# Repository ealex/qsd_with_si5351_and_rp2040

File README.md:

# qsd_with_si5351_and_rp2040
Tayloe QSD with SI5351 clock and RP2040 as an USB and UI controller

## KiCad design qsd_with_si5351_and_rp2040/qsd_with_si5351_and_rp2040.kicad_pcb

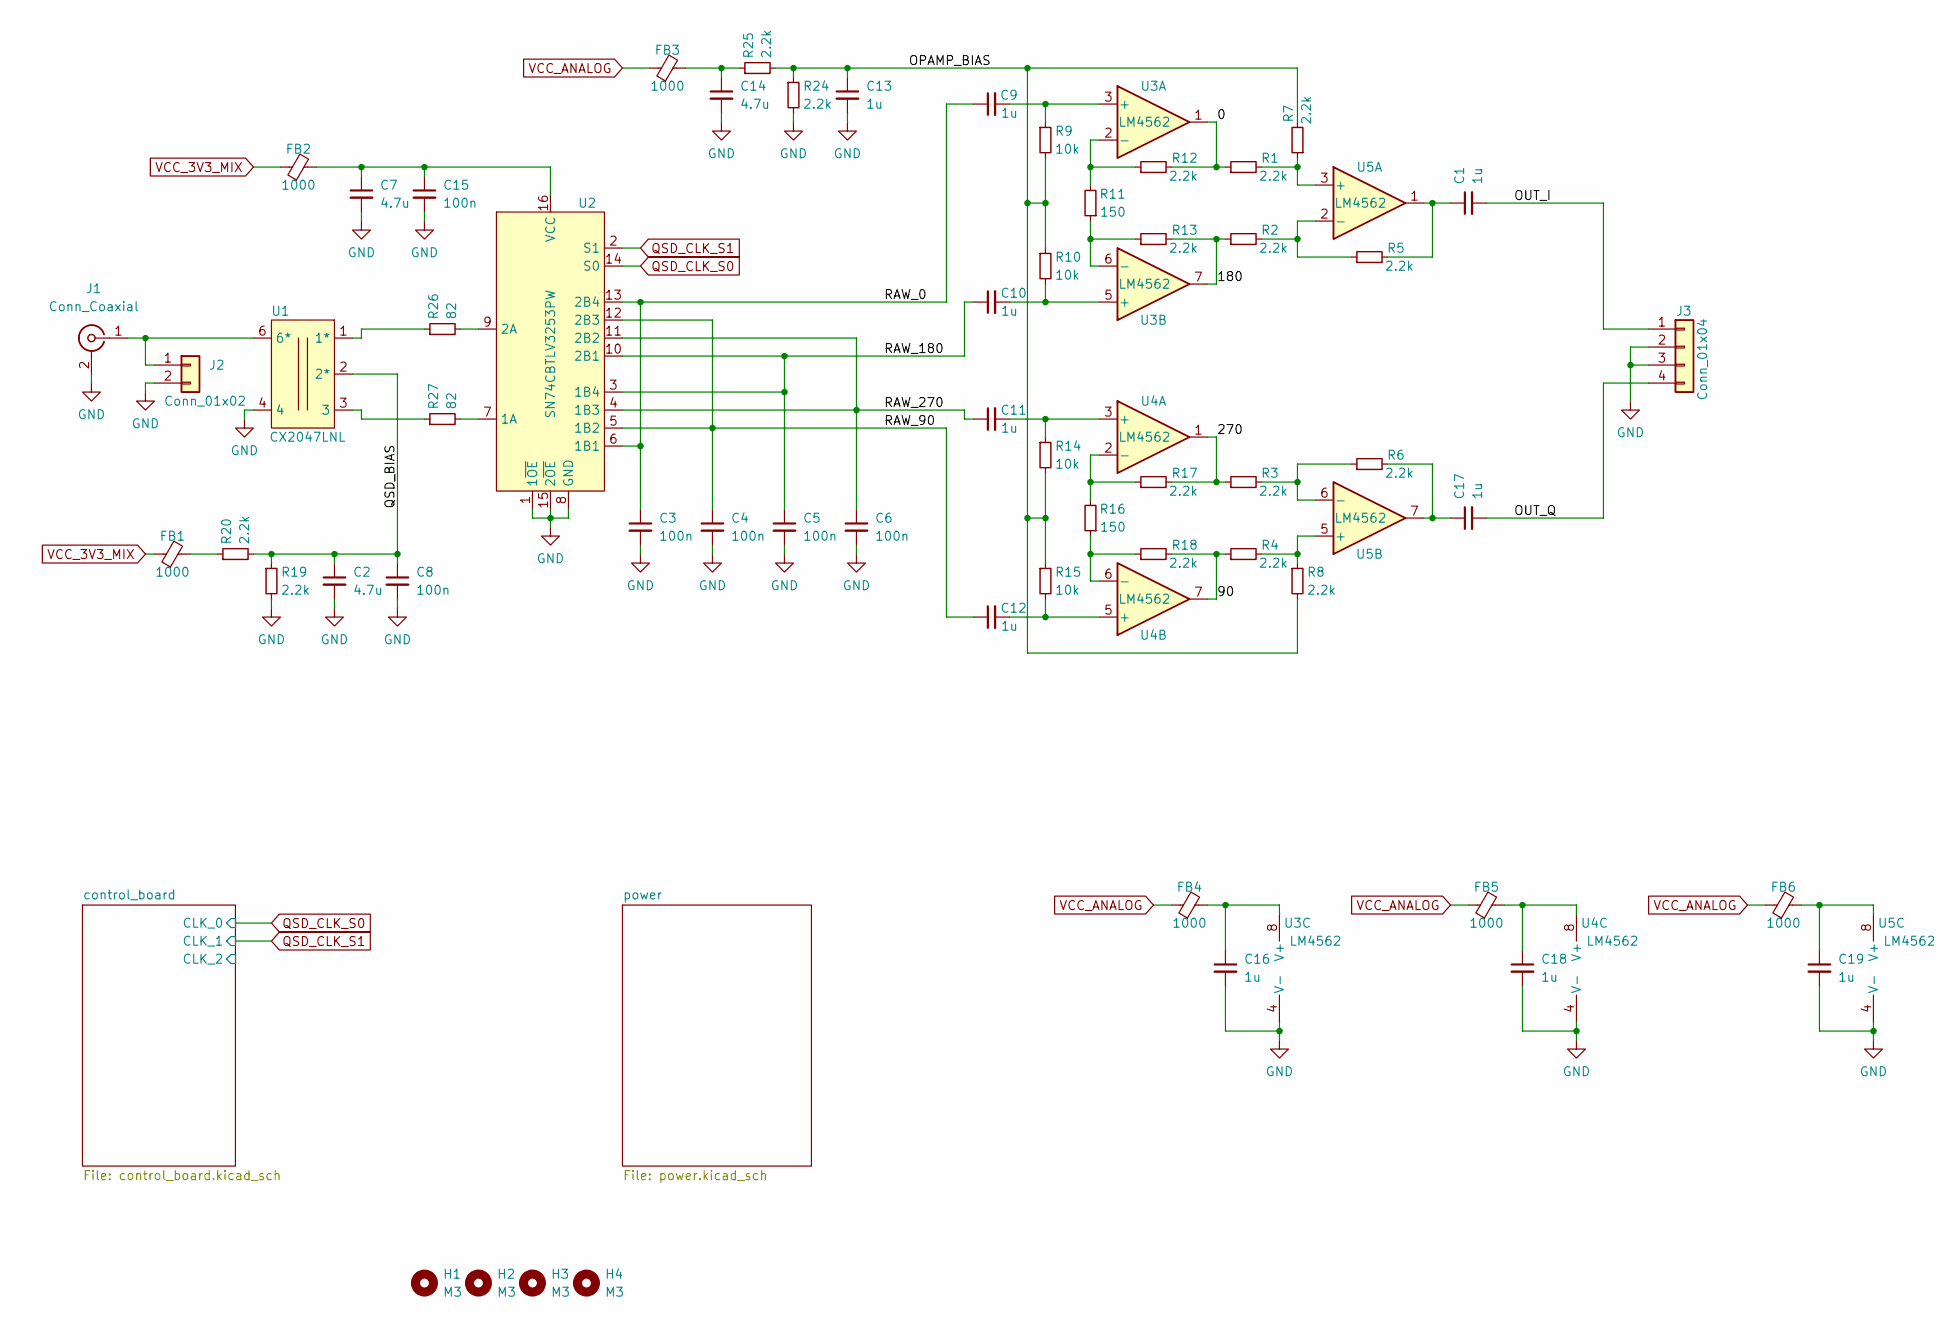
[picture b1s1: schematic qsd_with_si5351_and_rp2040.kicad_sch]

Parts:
C1, C9, C10, C11, C12, C13, C16, C17, C18, C19: 1u; C_0805_2012Metric
C2, C7, C14: 4.7u; C_0805_2012Metric
C3, C4, C5, C6, C8, C15: 100n; C_0805_2012Metric
FB1, FB2, FB3, FB4, FB5, FB6: 1000; L_0805_2012Metric_Pad1.05x1.20mm_HandSolder
H1, H2, H3, H4: M3; MountingHole_3.2mm_M3_DIN965_Pad_TopBottom
J1: Conn_Coaxial; 60312202114508
J2: Conn_01x02; PinHeader_1x02_P2.54mm_Vertical
J3: Conn_01x04; PinHeader_1x04_P2.54mm_Vertical
R1, R2, R3, R4, R5, R6, R7, R8, R12, R13, R17, R18, R19, R20, R24, R25: 2.2k; R_0805_2012Metric_Pad1.20x1.40mm_HandSolder
R9, R10, R14, R15: 10k; R_0805_2012Metric_Pad1.20x1.40mm_HandSolder
R11, R16: 150; R_0805_2012Metric_Pad1.20x1.40mm_HandSolder
R26, R27: 82; R_0805_2012Metric_Pad1.20x1.40mm_HandSolder
U1: CX2047LNL
U2: SN74CBTLV3253PW; TSSOP-16_4.4x5mm_P0.65mm
U3, U4, U5: LM4562; SO-8_3.9x4.9mm_P1.27mm

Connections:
/0: R1.1, R12.2, U3.1
/90: R4.1, R18.2, U4.7
/180: R2.1, R13.2, U3.7
/270: R3.1, R17.2, U4.1
/OPAMP_BIAS: C13.1, R7.2, R8.2, R9.2, R10.1, R14.2, R15.1, R24.1, R25.2
/OUT_I: C1.2, J3.1
/OUT_Q: C17.2, J3.4
/QSD_BIAS: C2.1, C8.1, R19.1, R20.2, U1.2 (2*)
/RAW_0: C3.1, C9.1, U2.6 (1B1), U2.13 (2B4)
/RAW_90: C4.1, C12.1, U2.5 (1B2), U2.12 (2B3)
/RAW_180: C5.1, C10.1, U2.3 (1B4), U2.10 (2B1)
/RAW_270: C6.1, C11.1, U2.4 (1B3), U2.11 (2B2)
unnamed: C1.1, R5.2, U5.1
unnamed: C9.2, R9.1, U3.3 (+)
unnamed: C10.2, R10.2, U3.5 (+)
unnamed: C11.2, R14.1, U4.3 (+)
unnamed: C12.2, R15.2, U4.5 (+)
unnamed: C14.1, FB3.2, R25.1
unnamed: C7.1, C15.1, FB2.2, U2.16 (VCC)
unnamed: C16.1, FB4.2, U3.8 (V+)
unnamed: C17.1, R6.2, U5.7
unnamed: C18.1, FB5.2, U4.8 (V+)
unnamed: C19.1, FB6.2, U5.8 (V+)
unnamed: FB1.2, R20.1
unnamed: J1.1 (In), J2.1, U1.6 (6*)
unnamed: R1.2, R7.1, U5.3 (+)
unnamed: R2.2, R5.1, U5.2 (-)
unnamed: R3.2, R6.1, U5.6 (-)
unnamed: R4.2, R8.1, U5.5 (+)
unnamed: R11.1, R13.1, U3.6 (-)
unnamed: R11.2, R12.1, U3.2 (-)
unnamed: R16.1, R18.1, U4.6 (-)
unnamed: R16.2, R17.1, U4.2 (-)
unnamed: R26.1, U1.1 (1*)
unnamed: R26.2, U2.9 (2A)
unnamed: R27.1, U1.3
unnamed: R27.2, U2.7 (1A)
QSD_CLK_S0: U2.14 (S0); also elsewhere on the board
QSD_CLK_S1: U2.2 (S1); also elsewhere on the board
VCC_3V3_MIX: FB1.1, FB2.1; also elsewhere on the board
VCC_ANALOG: FB3.1, FB4.1, FB5.1, FB6.1; also elsewhere on the board

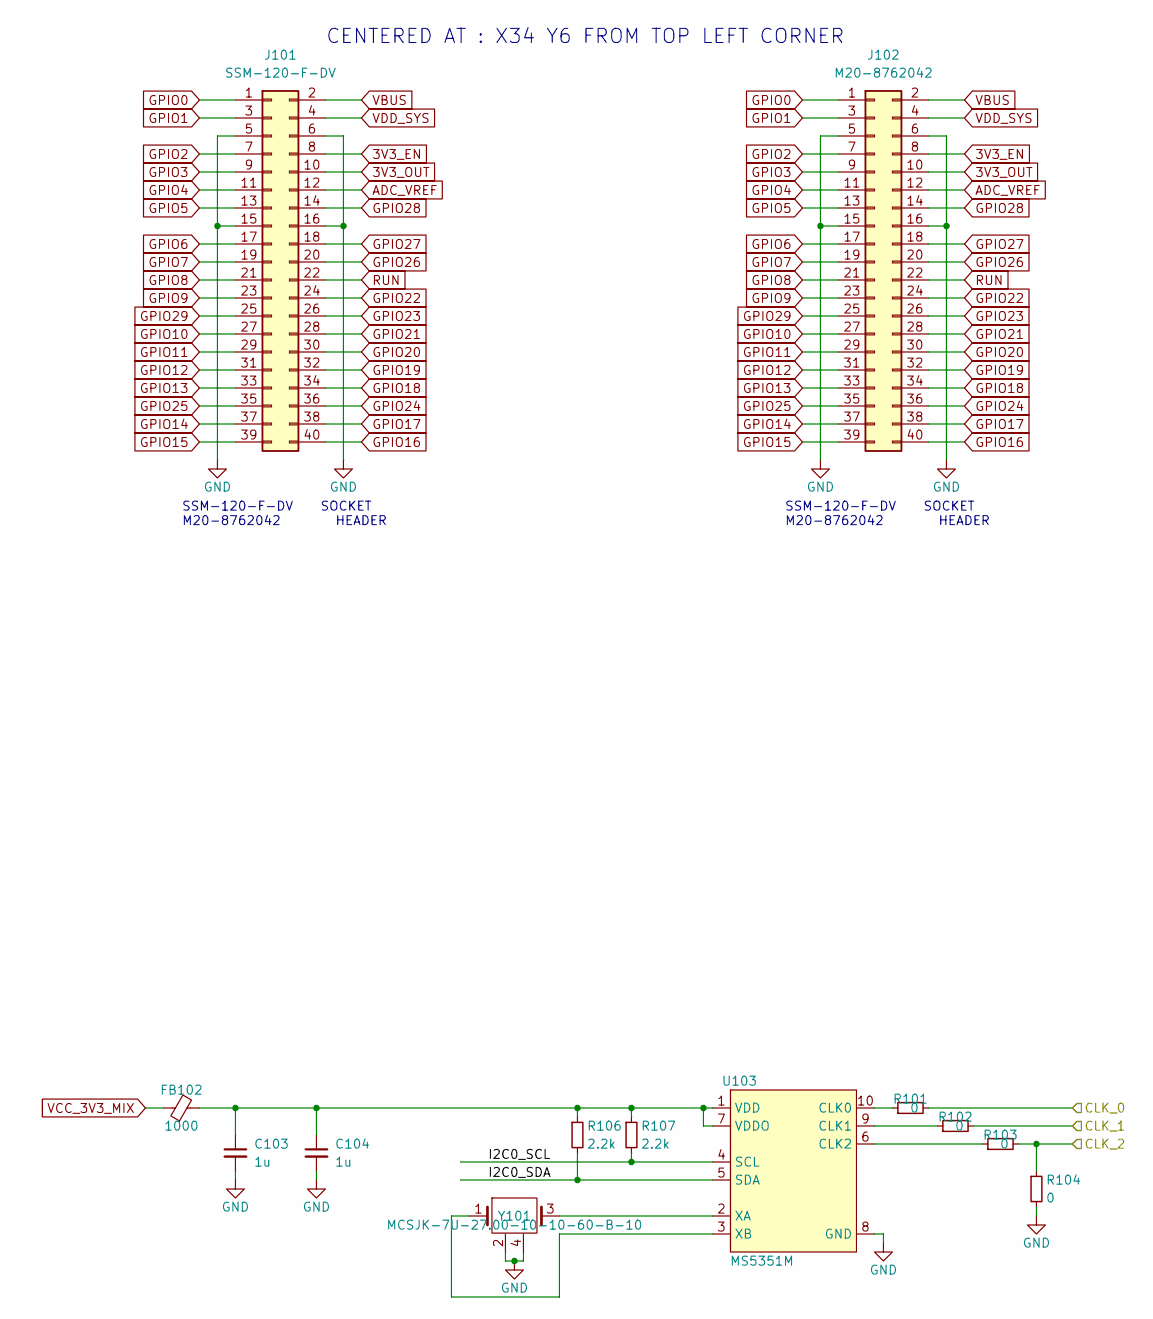
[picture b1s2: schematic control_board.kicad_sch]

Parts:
C103, C104: 1u; C_0805_2012Metric
FB102: 1000; L_0805_2012Metric_Pad1.05x1.20mm_HandSolder
J101: SSM-120-F-DV; PinSocket_2x20_P2.54mm_Vertical_SMD
J102: M20-8762042; PinHeader_2x20_P2.54mm_Vertical_SMD
R101, R102, R103, R104: 0; R_0805_2012Metric_Pad1.20x1.40mm_HandSolder
R106, R107: 2.2k; R_0805_2012Metric_Pad1.20x1.40mm_HandSolder
U103: MS5351M; MSOP-10_3x3mm_P0.5mm
Y101: MCSJK-7U-27.00-10-10-60-B-10; Crystal_SMD_3225-4Pin_3.2x2.5mm

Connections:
3V3_EN: J101.8, J102.8
3V3_OUT: J101.10, J102.10; also elsewhere on the board
/control_board/CLK_2: R103.2, R104.1
/control_board/I2C0_SCL: R107.2, U103.4 (SCL)
/control_board/I2C0_SDA: R106.2, U103.5 (SDA)
ADC_VREF: J101.12, J102.12
GPIO0: J101.1, J102.1
GPIO1: J101.3, J102.3
GPIO2: J101.7, J102.7
GPIO3: J101.9, J102.9
GPIO4: J101.11, J102.11
GPIO5: J101.13, J102.13
GPIO6: J101.17, J102.17
GPIO7: J101.19, J102.19
GPIO8: J101.21, J102.21
GPIO9: J101.23, J102.23
GPIO10: J101.27, J102.27
GPIO11: J101.29, J102.29
GPIO12: J101.31, J102.31
GPIO13: J101.33, J102.33
GPIO14: J101.37, J102.37
GPIO15: J101.39, J102.39
GPIO16: J101.40, J102.40
GPIO17: J101.38, J102.38
GPIO18: J101.34, J102.34
GPIO19: J101.32, J102.32
GPIO20: J101.30, J102.30
GPIO21: J101.28, J102.28
GPIO22: J101.24, J102.24
GPIO23: J101.26, J102.26
GPIO24: J101.36, J102.36
GPIO25: J101.35, J102.35
GPIO26: J101.20, J102.20
GPIO27: J101.18, J102.18
GPIO28: J101.14, J102.14
GPIO29: J101.25, J102.25
unnamed: R102.1, U103.9 (CLK1)
unnamed: R103.1, U103.6 (CLK2)
unnamed: C103.1, C104.1, FB102.2, R106.1, R107.1, U103.1 (VDD), U103.7 (VDDO)
unnamed: U103.2 (XA), Y101.3
unnamed: U103.3 (XB), Y101.1
unnamed: R101.1, U103.10 (CLK0)
QSD_CLK_S0: R101.2; also elsewhere on the board
QSD_CLK_S1: R102.2; also elsewhere on the board
RUN: J101.22, J102.22
VBUS: J101.2, J102.2
VCC_3V3_MIX: FB102.1; also elsewhere on the board
VDD_SYS: J101.4, J102.4; also elsewhere on the board

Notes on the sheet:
SSM-120-F-DV SOCKET M20-8762042 HEADER
CENTERED AT : X34 Y6 FROM TOP LEFT CORNER

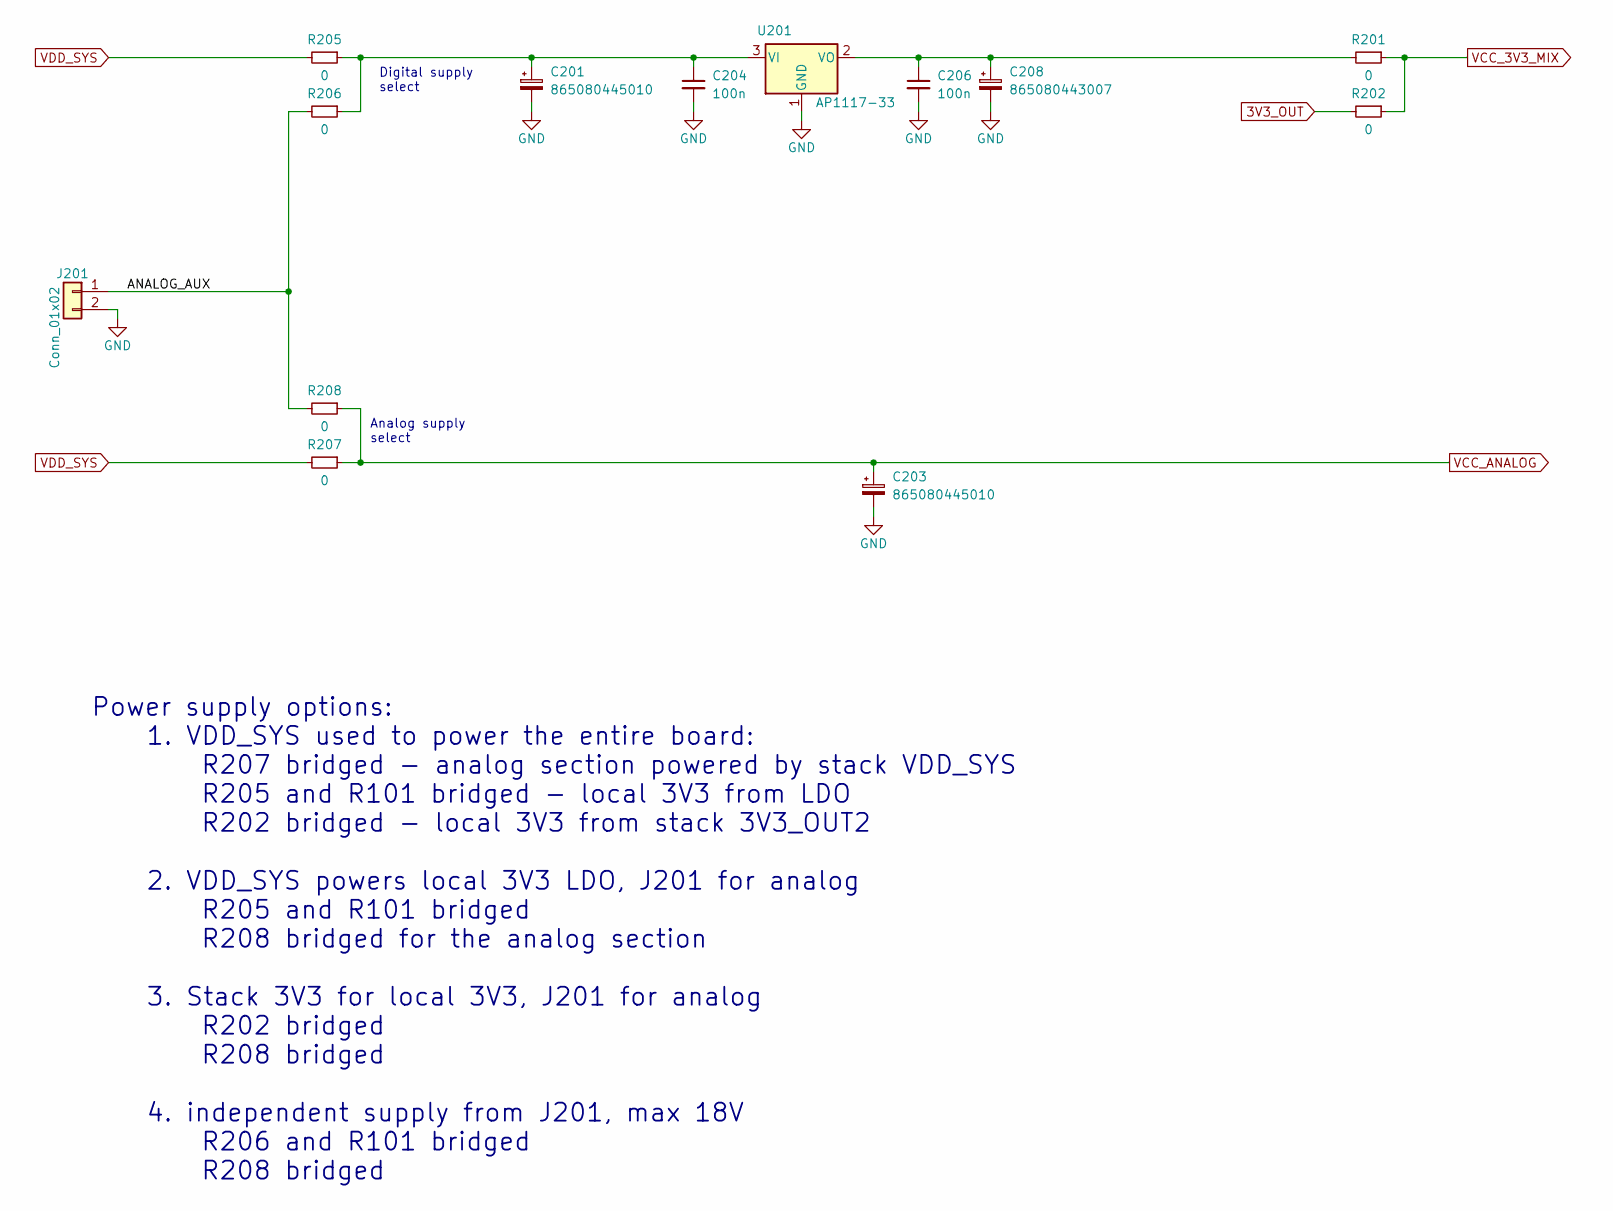
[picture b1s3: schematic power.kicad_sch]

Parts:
C201, C203: 865080445010
C204, C206: 100n; C_0805_2012Metric_Pad1.18x1.45mm_HandSolder
C208: 865080443007
J201: Conn_01x02; PinHeader_1x02_P2.54mm_Vertical
R201, R202, R205, R206, R207, R208: 0; R_0805_2012Metric_Pad1.20x1.40mm_HandSolder
U201: AP1117-33; SOT-223-3_TabPin2

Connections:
3V3_OUT: R202.2; also elsewhere on the board
/power/ANALOG_AUX: J201.1, R206.2, R208.2
unnamed: C206.1, C208.1, R201.2, U201.2 (VO)
unnamed: C201.1, C204.1, R205.1, R206.1, U201.3 (VI)
VCC_3V3_MIX: R201.1, R202.1; also elsewhere on the board
VCC_ANALOG: C203.1, R207.1, R208.1; also elsewhere on the board
VDD_SYS: R205.2, R207.2; also elsewhere on the board

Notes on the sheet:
Digital supply select
Power supply options: 1. VDD_SYS used to power the entire board: R207 bridged - analog section powered by stack VDD_SYS R205 and R101 bridged - local 3V3 from LDO R202 bridged - local 3V3 from stack 3V3_OUT2 2. VDD_SYS powers local 3V3 LDO, J201 for analog R205 and R101 bridged R208 bridged for the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
Analog supply select

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
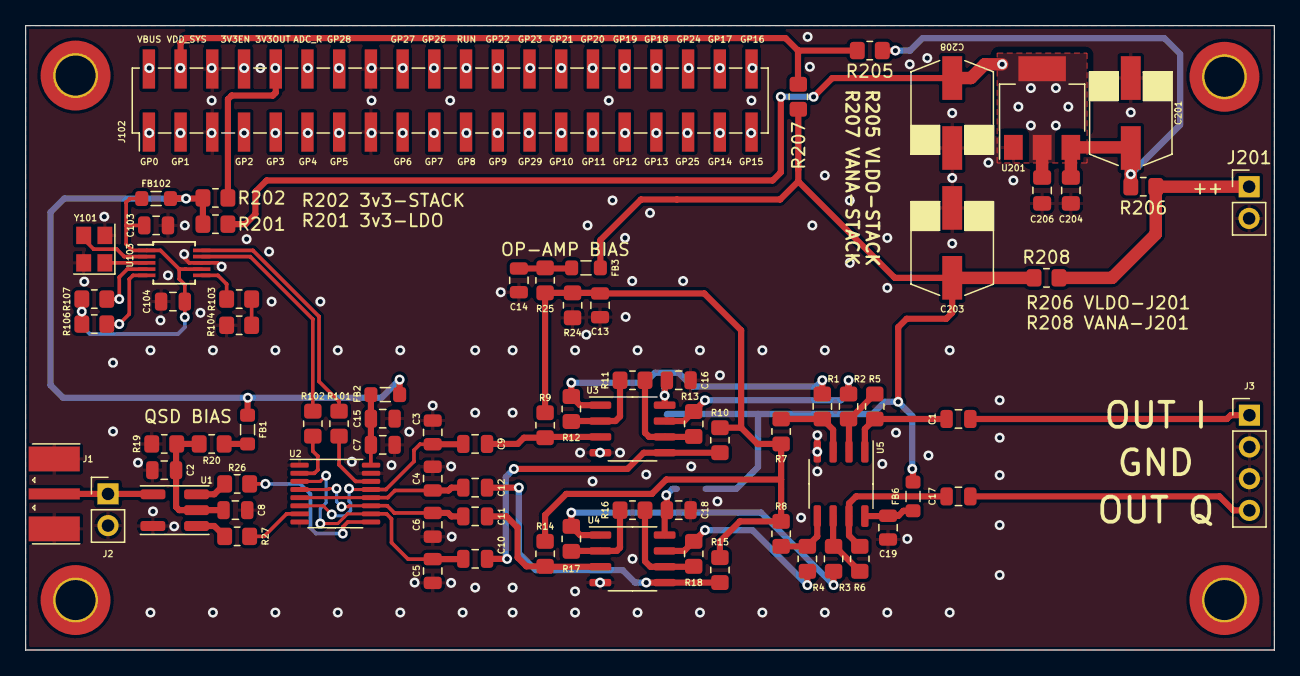
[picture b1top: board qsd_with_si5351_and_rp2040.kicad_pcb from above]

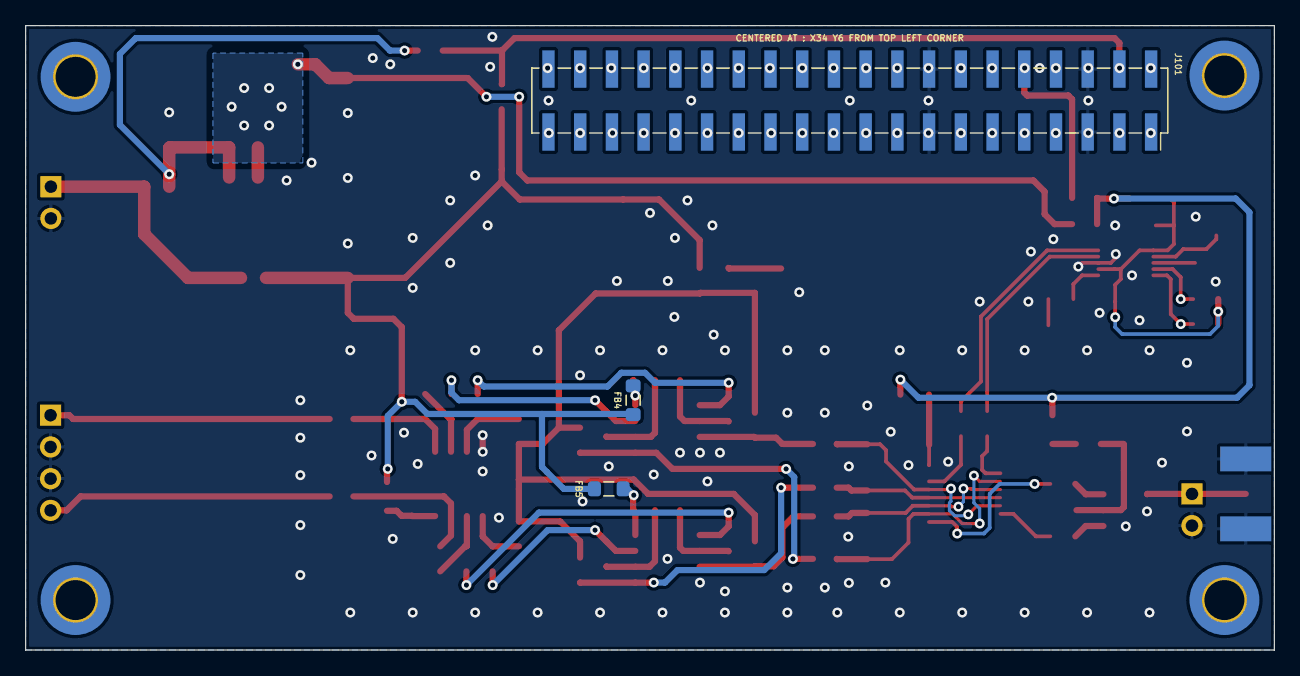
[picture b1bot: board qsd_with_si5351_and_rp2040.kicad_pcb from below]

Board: 2 copper layers, 100.0 x 50.0 mm, 87 parts (3 on the bottom side), 90 nets.

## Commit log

2024-02-12 add refference material and datasheets
2024-02-12 add extra source
2024-02-12 add usb-c connector
2024-02-12 remove unused libraries
2024-02-13 add rp2040 related parts
2024-02-13 start working on the schematic
2024-02-15 schematic ~ done - try some layout
2024-02-15 version with stackable connector
2024-02-15 update psf
2024-02-19 ready for production
2024-02-19 production data
